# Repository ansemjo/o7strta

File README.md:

# O7STRTA

This is a silly seven-segment display that I soldered as a present for a friend.
It's just a shift register and a couple of LEDs.

Afterwards, I created a schematic in KiCad and mocked up a PCB to create a
rendering of what it looked like.

* [My notes and sketches](sketches.pdf)
* [Mock-up datasheet](O7STRTA%20Seven%20Segment.pdf)
* [Example script to interface with an FT232H](hello.py)

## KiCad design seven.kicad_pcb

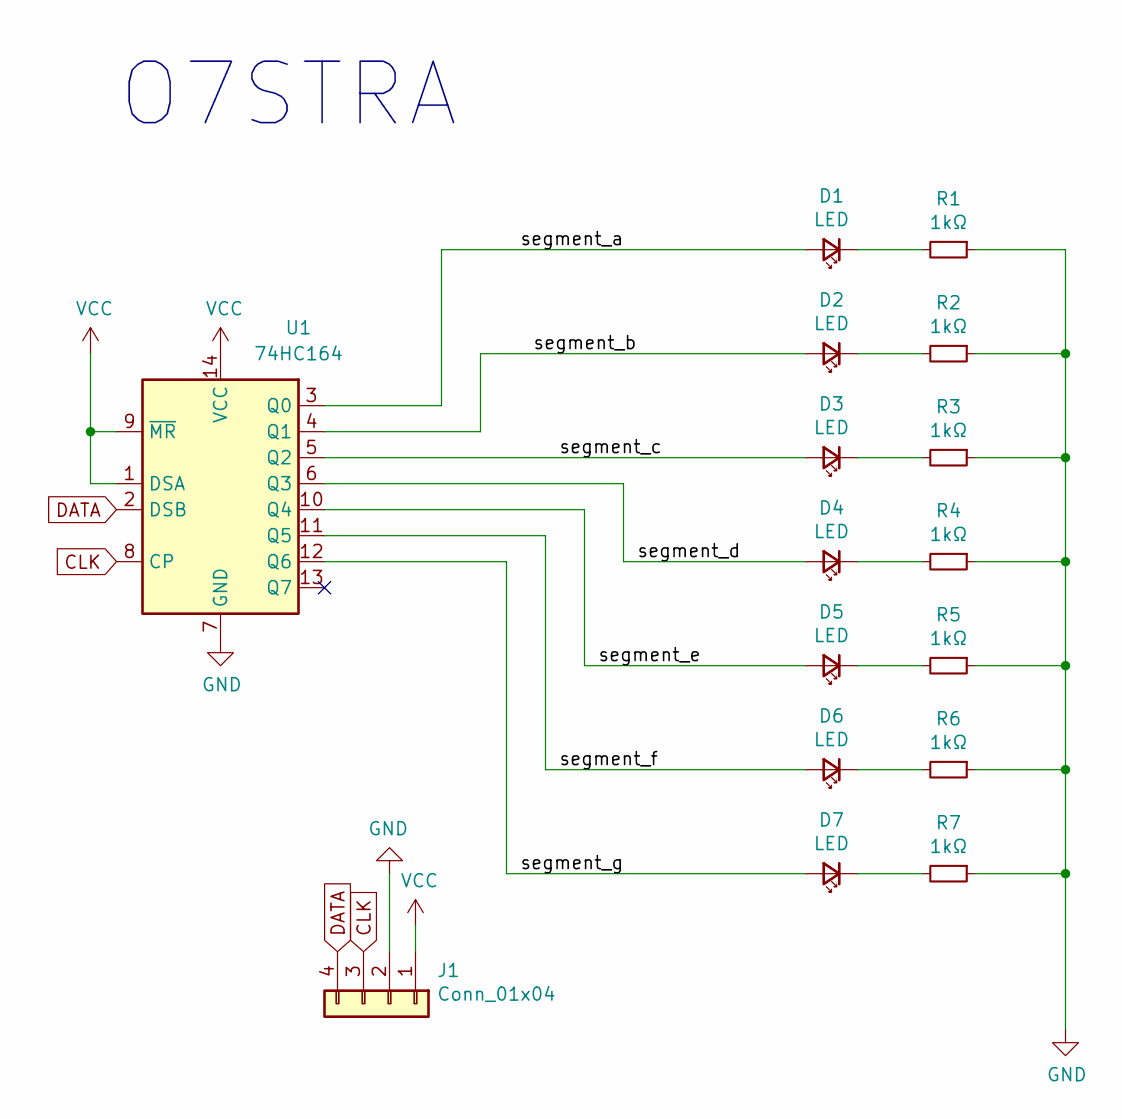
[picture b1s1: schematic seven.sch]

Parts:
D1, D2, D3, D4, D5, D6, D7: LED; LED_Rectangular_W5.0mm_H2.0mm
J1: Conn_01x04; PinHeader_1x04_P2.54mm_Horizontal
R1, R2, R3, R4, R5, R6, R7: 1kΩ; R_Axial_DIN0207_L6.3mm_D2.5mm_P2.54mm_Vertical
U1: 74HC164; DIP-14_W7.62mm

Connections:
/segment_a: D1.2 (A), U1.3 (Q0)
/segment_b: D2.2 (A), U1.4 (Q1)
/segment_c: D3.2 (A), U1.5 (Q2)
/segment_d: D4.2 (A), U1.6 (Q3)
/segment_e: D5.2 (A), U1.10 (Q4)
/segment_f: D6.2 (A), U1.11 (Q5)
/segment_g: D7.2 (A), U1.12 (Q6)
CLK: J1.3, U1.8 (CP)
DATA: J1.4, U1.2 (DSB)
GND: J1.2, R1.1, R2.1, R3.1, R4.1, R5.1, R6.1, R7.1, U1.7 (GND)
unnamed: D1.1 (K), R1.2
unnamed: D2.1 (K), R2.2
unnamed: D3.1 (K), R3.2
unnamed: D4.1 (K), R4.2
unnamed: D5.1 (K), R5.2
unnamed: D6.1 (K), R6.2
unnamed: D7.1 (K), R7.2
VCC: J1.1, U1.1 (DSA), U1.9 (~MR), U1.14 (VCC)

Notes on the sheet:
O7STRA

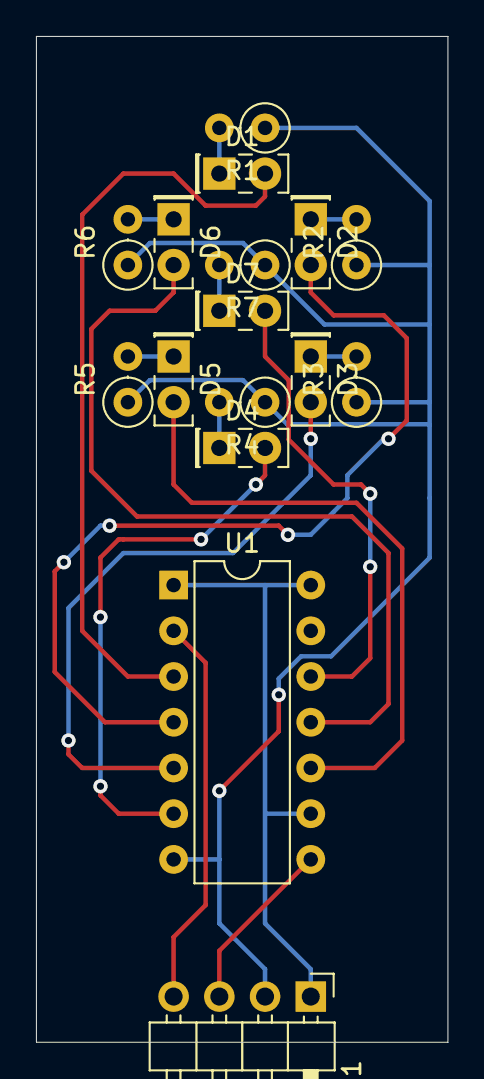
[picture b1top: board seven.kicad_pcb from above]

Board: 2 copper layers, 22.9 x 55.9 mm, 16 parts (0 on the bottom side), 18 nets.

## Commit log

2020-07-17 add files made for maltes birthday
2020-07-17 recreate the board in kicad
2020-07-17 add sketches pdf and photos
2020-09-28 add readme
2020-09-28 remove fp-info-cache and add ignores
